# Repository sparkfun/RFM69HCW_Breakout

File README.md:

RFM69HCW Breakout Board
=================
The RFM69HCW is an inexpensive and versatile radio module that operates in the unlicensed ISM (Industry, Science, and Medicine) radio band. It's perfect for building inexpensive short-range wireless networks of sensors and actuators for home automation, citizen science, and more.

Specs
----------------

* Transmit power: -18dBm (0.016mW) to +20dBm (100mW) in 1dBm steps
* Receive sensitivity: down to -120dBm at 1.2kbps
* Modulation types: FSK GFSK MSK GMSK OOK
* Bit rates (FSK): 1.2kbps to 300kbps
* Voltage range: 1.8V to 3.6V
* Current consumption: 0.1uA sleep, 1.25mA standby, 16mA receive, 
* 130mA transmit (max)
* Encryption: AES 128-bit (optional)
* Packet buffer (FIFO): 66 bytes
* Dimensions: 0.8" x 1.1"

Product Versions
----------------

The RFM69HCW modules transmit in the [ISM band](http://en.wikipedia.org/wiki/ISM_band), which is reserved for short-range, low-power communications. SparkFun sells the RFM69HCW Breakout Board in two frequencies:

* [**RFM69HCW Breakout 915MHz (WRL-12775)**](https://www.sparkfun.com/products/12775)
* [**RFM69HCW Breakout 433MHz (WRL-12823)**](https://www.sparkfun.com/products/12823)

Broadly speaking, the 915MHz version is legal in [ITU region](http://en.wikipedia.org/wiki/ITU_region) 2 (North and South America, Australia, Greenland, Pacific Islands, Israel), and the 433MHz version is legal in [ITU region](http://en.wikipedia.org/wiki/ITU_region) 1 (Europe, Africa, Middle East, Russia). Other areas have mixed allocations; hobbyist use is not likely to be an issue, but if you're going to be deploying a lot of these or using them in a commercial product, check your local regulations.

Documentation
-------------------

* [**Hookup Guide**](https://learn.sparkfun.com/tutorials/rfm69hcw-hookup-guide)
* [**RFM69HCW Breakout Board Schematic**](https://github.com/sparkfun/RFM69HCW_Breakout/blob/master/documentation/RFM69HCW_BOB.pdf)
* [**RFM69HCW datasheet**](https://github.com/sparkfun/RFM69HCW_Breakout/blob/master/documentation/RFM69HCW-V1.1.pdf)
* [**HopeRF RFM69HCW product page (external link)**](http://www.hoperf.com/rf/fsk_module/RFM69HCW.htm)

Repository Contents
-------------------
* [**/Libraries/Arduino**](https://github.com/sparkfun/RFM69HCW_Breakout/tree/master/Libraries/Arduino) - Contains the [RFM69 library](https://github.com/LowPowerLab/RFM69) written by Felix Rusu of [LowPowerLab.com](lowpowerlab.com). See [https://github.com/LowPowerLab/RFM69](https://github.com/LowPowerLab/RFM69) for the most up-to-date version.

* [**/Libraries/Arduino/RFM69/examples**](https://github.com/sparkfun/RFM69HCW_Breakout/tree/master/Libraries/Arduino/RFM69/examples) - Example Arduino sketch showing how to use the SparkFun RFM69HCW breakout board. See the hook-up guide at [https://learn.sparkfun.com/tutorials/rfm69hcw-hookup-guide](https://learn.sparkfun.com/tutorials/rfm69hcw-hookup-guide) for wiring and usage details.

* [**/hardware**](https://github.com/sparkfun/RFM69HCW_Breakout/tree/master/hardware) - Eagle design files (.brd, .sch)

* [**/documentation**](https://github.com/sparkfun/RFM69HCW_Breakout/tree/master/documentation) - Datasheets, schematic, etc.

Attribution
-----------
We gratefully acknowledge Felix Rusu of [LowPowerLab.com](lowpowerlab.com) for his terrific [RFM69 library](https://github.com/LowPowerLab/RFM69), which runs on his very cool [Moteino](http://lowpowerlab.com/moteino/) hardware. A version of his library is included here for the convenience of SparkFun customers. Please see his [GitHub repository](https://github.com/LowPowerLab/RFM69) for the latest version.

License Information
-------------------
The hardware design is released under the [Creative Commons Attribution-ShareAlike 4.0 International](http://creativecommons.org/licenses/by-sa/4.0/) license.

Felix Rusu's RFM69 library is released under the [Creative Commons Attribution-ShareAlike 3.0](http://creativecommons.org/licenses/by-sa/3.0/) license. 

SparkFun's example code is based on Felix Rusu's work, and is thus released under the same [Creative Commons Attribution-ShareAlike 3.0](http://creativecommons.org/licenses/by-sa/3.0/) license.

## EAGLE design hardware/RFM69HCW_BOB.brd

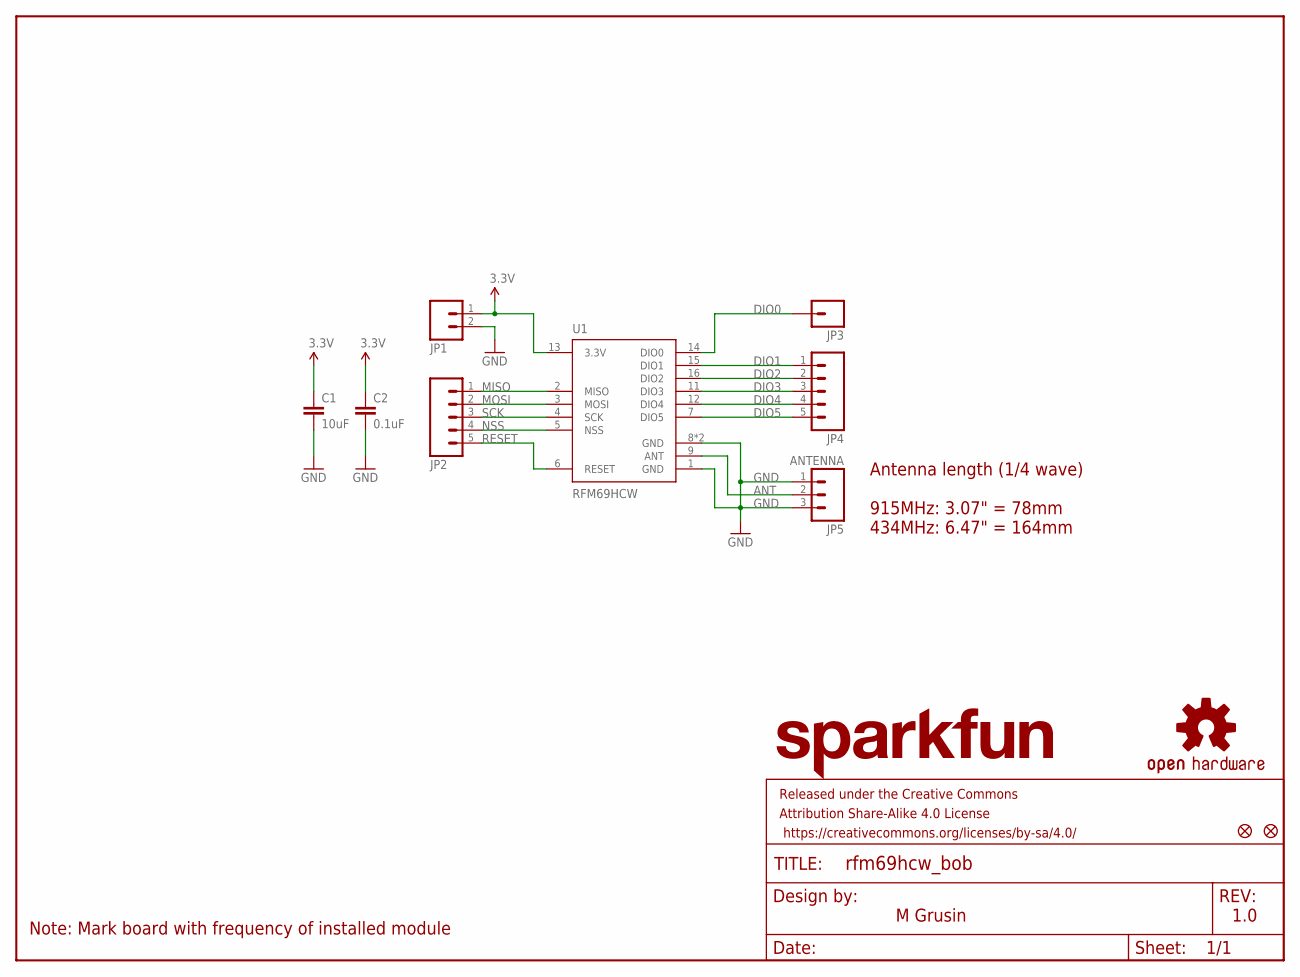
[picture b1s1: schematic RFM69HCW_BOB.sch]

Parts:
C1: 10uF; 1210
C2: 0.1uF; 0603-CAP
FID1, FID2: FIDUCIAL1X2; FIDUCIAL-1X2
FRAME1: FRAME-LETTER; CREATIVE_COMMONS
JP1: M021X02_NO_SILK; 1X02_NO_SILK
JP2, JP4: M05_ROUNDONLY_NOSILK; 1X05_ROUNDONLY_NOSILK
JP3: M01SMDNS; 1X01NS
JP5: ANTENNA; 1X03_ROUND_ONLY_NO_SILK
LOGO1: SFE_LOGO_NAME.1_INCH; SFE_LOGO_NAME_.1
LOGO2: OSHW-LOGOS; OSHW-LOGO-S
U1: RFM69HCW; RFM69HCW-XXXS2

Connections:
3.3V: C1.1, C2.1, JP1.1, U1.13 (3.3V)
ANT: JP5.2, U1.9 (ANT)
DIO0: JP3.1, U1.14 (DIO0)
DIO1: JP4.1, U1.15 (DIO1)
DIO2: JP4.2, U1.16 (DIO2)
DIO3: JP4.3, U1.11 (DIO3)
DIO4: JP4.4, U1.12 (DIO4)
DIO5: JP4.5, U1.7 (DIO5)
GND: C1.2, C2.2, JP1.2, JP5.1, JP5.3, U1.1 (GND), U1.8 (GND), U1.10 (GND)
MISO: JP2.1, U1.2 (MISO)
MOSI: JP2.2, U1.3 (MOSI)
NSS: JP2.4, U1.5 (NSS)
RESET: JP2.5, U1.6 (RESET)
SCK: JP2.3, U1.4 (SCK)

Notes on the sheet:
M Grusin
1.0
Note: Mark board with frequency of installed module
Antenna length (1/4 wave) 915MHz: 3.07" = 78mm 434MHz: 6.47" = 164mm

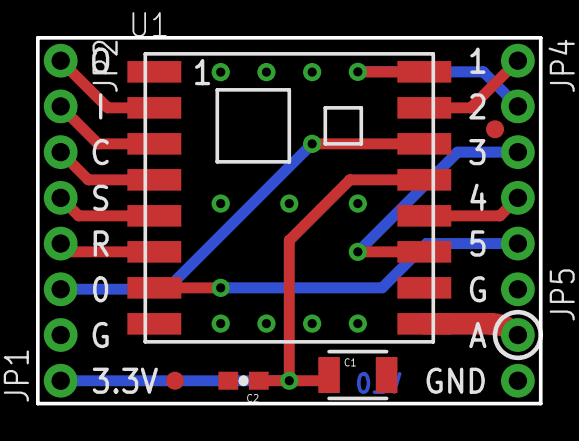
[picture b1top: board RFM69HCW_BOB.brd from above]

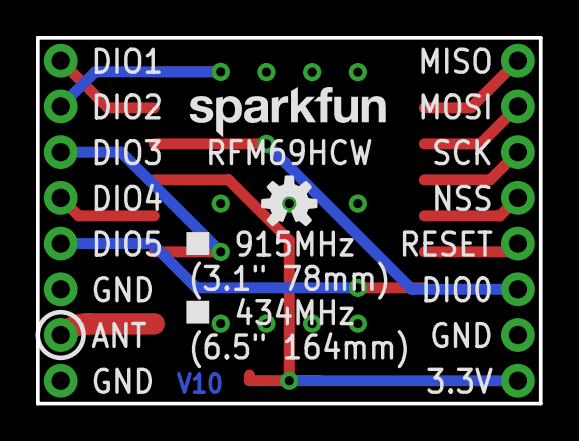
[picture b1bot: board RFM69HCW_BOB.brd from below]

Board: 2 copper layers, 27.9 x 20.3 mm, 13 parts (2 on the bottom side), 14 nets.

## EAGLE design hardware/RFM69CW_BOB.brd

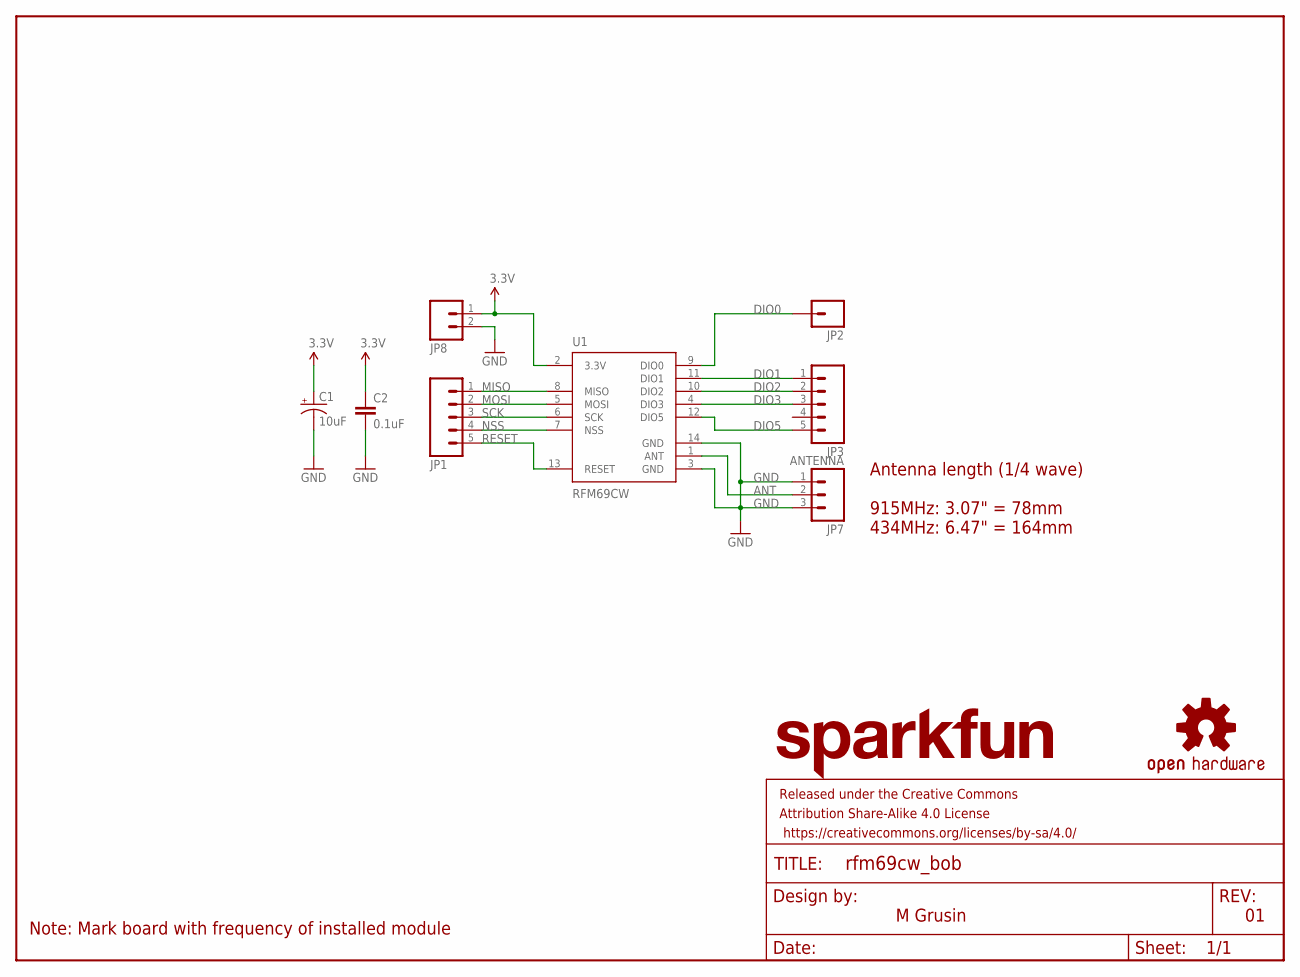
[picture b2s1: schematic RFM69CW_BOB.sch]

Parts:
C1: 10uF; EIA3216
C2: 0.1uF; 0603-CAP
FRAME1: FRAME-LETTER; CREATIVE_COMMONS
JP1, JP3: M05_ROUNDONLY_NOSILK; 1X05_ROUNDONLY_NOSILK
JP2: M01SMDNS; 1X01NS
JP7: ANTENNA; 1X03_ROUND_ONLY_NO_SILK
JP8: M021X02_NO_SILK; 1X02_NO_SILK
LOGO1: SFE_LOGO_NAME.1_INCH; SFE_LOGO_NAME_.1
LOGO2: OSHW-LOGOS; OSHW-LOGO-S
U1: RFM69CW; RFM69CW-XXXS2

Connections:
3.3V: C1.A (+), C2.1, JP8.1, U1.2 (3.3V)
ANT: JP7.2, U1.1 (ANT)
DIO0: JP2.1, U1.9 (DIO0)
DIO1: JP3.1, U1.11 (DIO1)
DIO2: JP3.2, U1.10 (DIO2)
DIO3: JP3.3, U1.4 (DIO3)
DIO5: JP3.5, U1.12 (DIO5)
GND: C1.C (-), C2.2, JP7.1, JP7.3, JP8.2, U1.3 (GND), U1.14 (GND)
MISO: JP1.1, U1.8 (MISO)
MOSI: JP1.2, U1.5 (MOSI)
NSS: JP1.4, U1.7 (NSS)
RESET: JP1.5, U1.13 (RESET)
SCK: JP1.3, U1.6 (SCK)

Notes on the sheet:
M Grusin
Note: Mark board with frequency of installed module
Antenna length (1/4 wave) 915MHz: 3.07" = 78mm 434MHz: 6.47" = 164mm

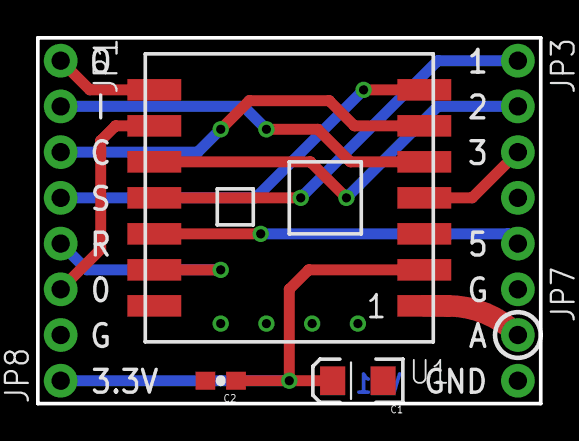
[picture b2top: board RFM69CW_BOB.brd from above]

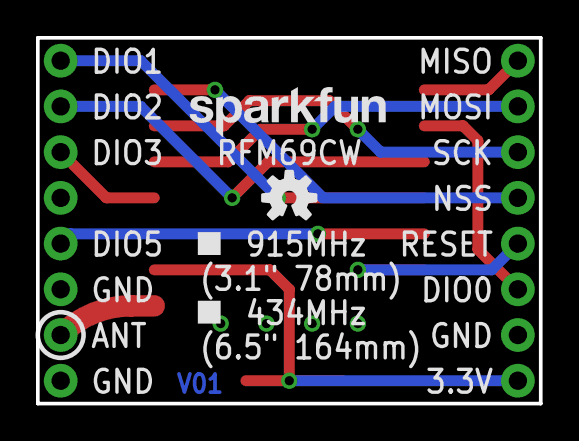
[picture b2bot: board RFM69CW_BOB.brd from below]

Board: 2 copper layers, 27.9 x 20.3 mm, 11 parts (2 on the bottom side), 13 nets.

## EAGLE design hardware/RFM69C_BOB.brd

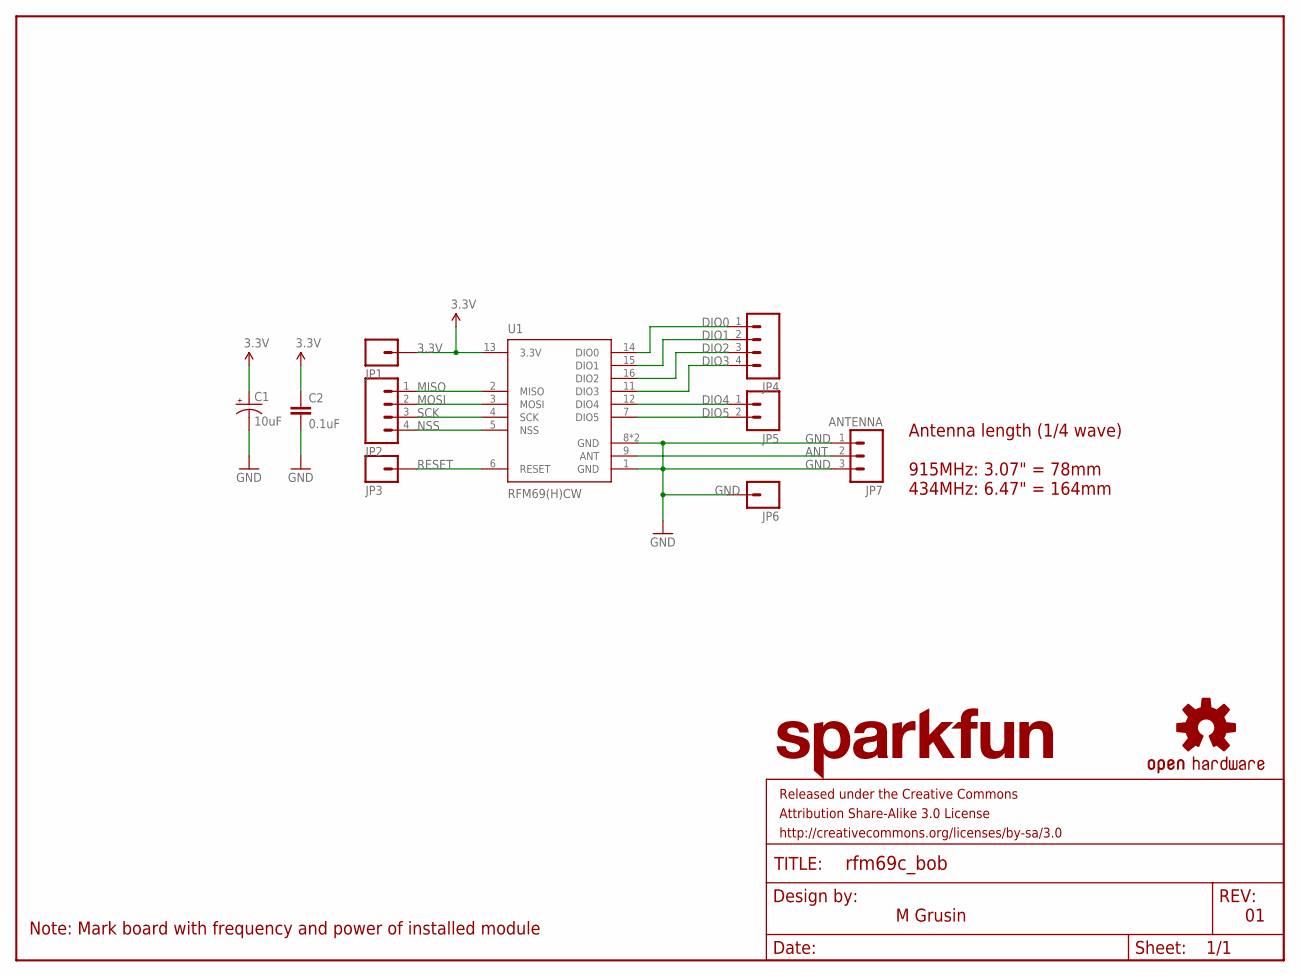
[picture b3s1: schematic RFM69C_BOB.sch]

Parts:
C1: 10uF; EIA3216
C2: 0.1uF; 0603-CAP
FRAME1: FRAME-LETTER; CREATIVE_COMMONS
JP1, JP3, JP6: M01SMDNS; 1X01NS
JP2, JP4: M041X04_NO_SILK_ROUND; 1X04_NO_SILK_ROUND
JP5: M021X02_NO_SILK; 1X02_NO_SILK
JP7: ANTENNA; 1X03_ROUND_ONLY_NO_SILK
LOGO1: SFE_LOGO_NAME.1_INCH; SFE_LOGO_NAME_.1
LOGO2: OSHW-LOGOS; OSHW-LOGO-S
U1: RFM69(H)CW; RFM69CS2

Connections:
3.3V: C1.A (+), C2.1, JP1.1, U1.13 (3.3V)
ANT: JP7.2, U1.9 (ANT)
DIO0: JP4.1, U1.14 (DIO0)
DIO1: JP4.2, U1.15 (DIO1)
DIO2: JP4.3, U1.16 (DIO2)
DIO3: JP4.4, U1.11 (DIO3)
DIO4: JP5.1, U1.12 (DIO4)
DIO5: JP5.2, U1.7 (DIO5)
GND: C1.C (-), C2.2, JP6.1, JP7.1, JP7.3, U1.1 (GND), U1.8 (GND), U1.10 (GND)
MISO: JP2.1, U1.2 (MISO)
MOSI: JP2.2, U1.3 (MOSI)
NSS: JP2.4, U1.5 (NSS)
RESET: JP3.1, U1.6 (RESET)
SCK: JP2.3, U1.4 (SCK)

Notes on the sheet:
M Grusin
Note: Mark board with frequency and power of installed module
Antenna length (1/4 wave) 915MHz: 3.07" = 78mm 434MHz: 6.47" = 164mm

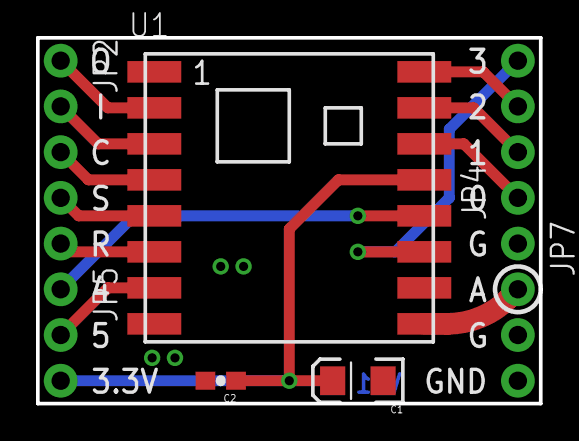
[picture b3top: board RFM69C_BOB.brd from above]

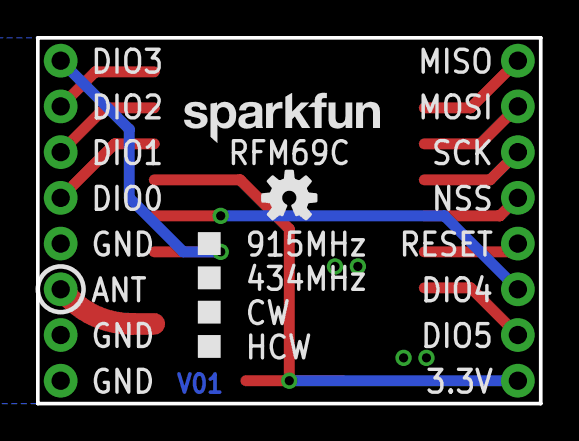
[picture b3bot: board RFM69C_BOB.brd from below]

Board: 2 copper layers, 27.9 x 20.3 mm, 13 parts (2 on the bottom side), 14 nets.

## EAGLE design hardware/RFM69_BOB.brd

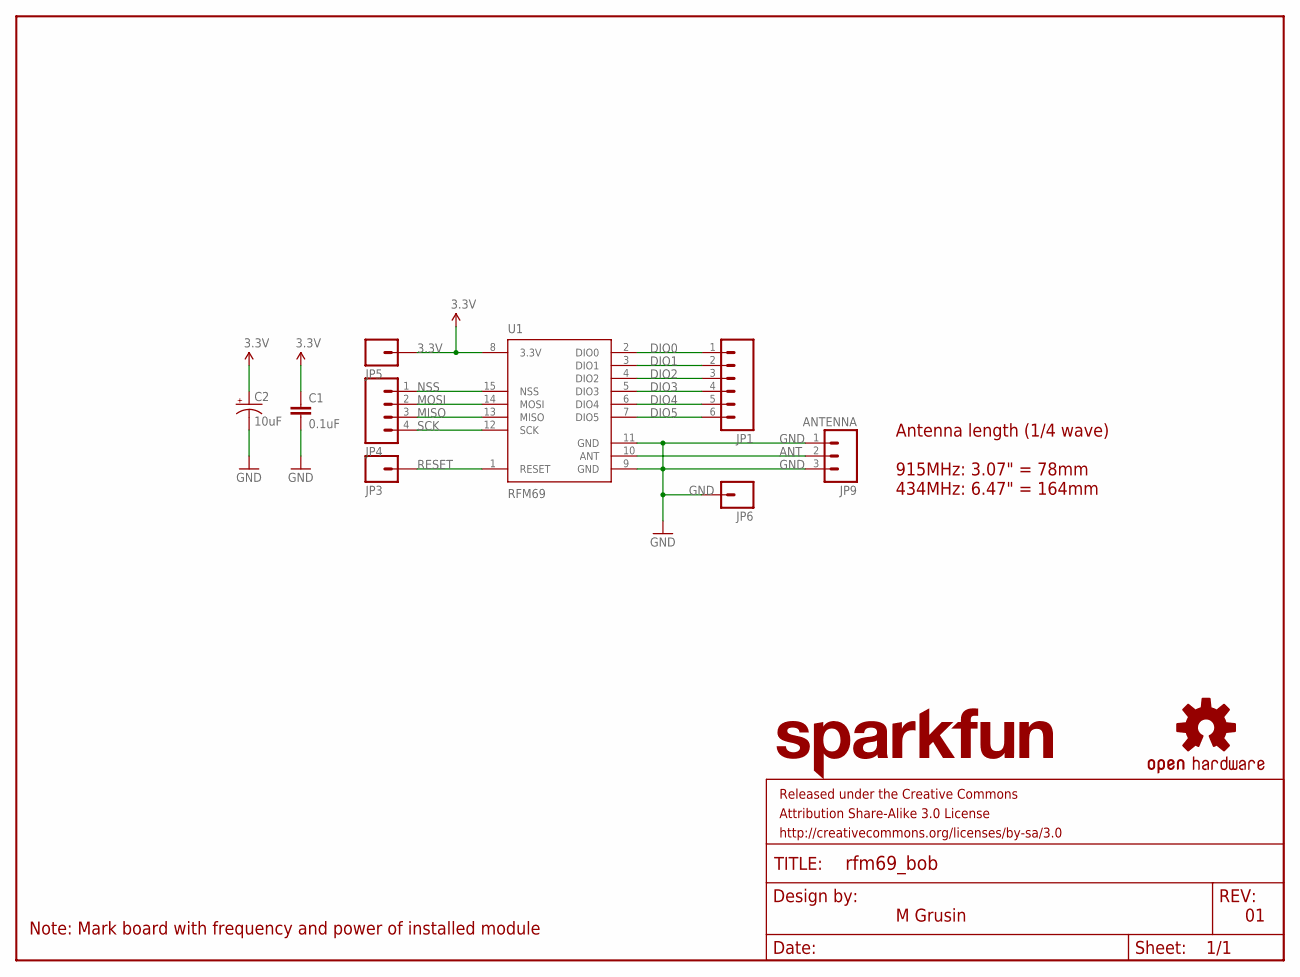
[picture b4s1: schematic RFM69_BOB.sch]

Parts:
C1: 0.1uF; 0603-CAP
C2: 10uF; EIA3216
FRAME1: FRAME-LETTER; CREATIVE_COMMONS
JP1: M06_NOSILK_ROUND; 1X06_NO_SILK_ROUND
JP3, JP5, JP6: M01SMDNS; 1X01NS
JP4: M041X04_NO_SILK_ROUND; 1X04_NO_SILK_ROUND
JP9: ANTENNA; 1X03_ROUND_ONLY_NO_SILK
LOGO1: SFE_LOGO_NAME.1_INCH; SFE_LOGO_NAME_.1
LOGO2: OSHW-LOGOS; OSHW-LOGO-S
U1: RFM69

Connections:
3.3V: C1.1, C2.A (+), JP5.1, U1.8 (3.3V)
ANT: JP9.2, U1.10 (ANT)
DIO0: JP1.1, U1.2 (DIO0)
DIO1: JP1.2, U1.3 (DIO1)
DIO2: JP1.3, U1.4 (DIO2)
DIO3: JP1.4, U1.5 (DIO3)
DIO4: JP1.5, U1.6 (DIO4)
DIO5: JP1.6, U1.7 (DIO5)
GND: C1.2, C2.C (-), JP6.1, JP9.1, JP9.3, U1.9 (GND), U1.11 (GND)
MISO: JP4.3, U1.13 (MISO)
MOSI: JP4.2, U1.14 (MOSI)
NSS: JP4.1, U1.15 (NSS)
RESET: JP3.1, U1.1 (RESET)
SCK: JP4.4, U1.12 (SCK)

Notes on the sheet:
M Grusin
Note: Mark board with frequency and power of installed module
Antenna length (1/4 wave) 915MHz: 3.07" = 78mm 434MHz: 6.47" = 164mm

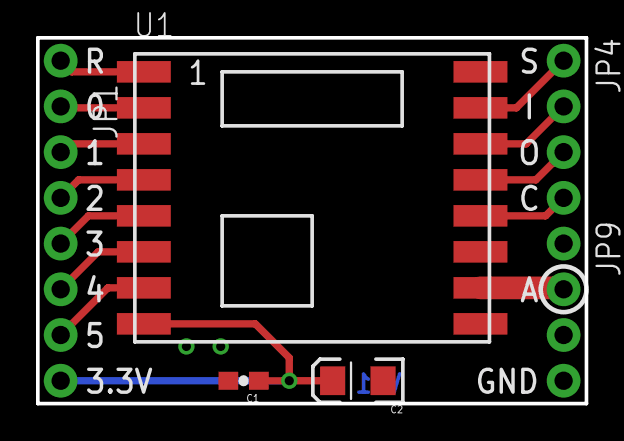
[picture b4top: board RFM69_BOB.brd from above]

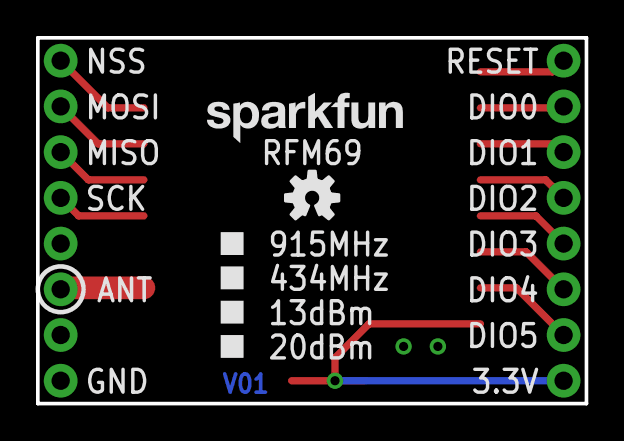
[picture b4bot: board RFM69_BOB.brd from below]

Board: 2 copper layers, 30.5 x 20.3 mm, 12 parts (2 on the bottom side), 14 nets.

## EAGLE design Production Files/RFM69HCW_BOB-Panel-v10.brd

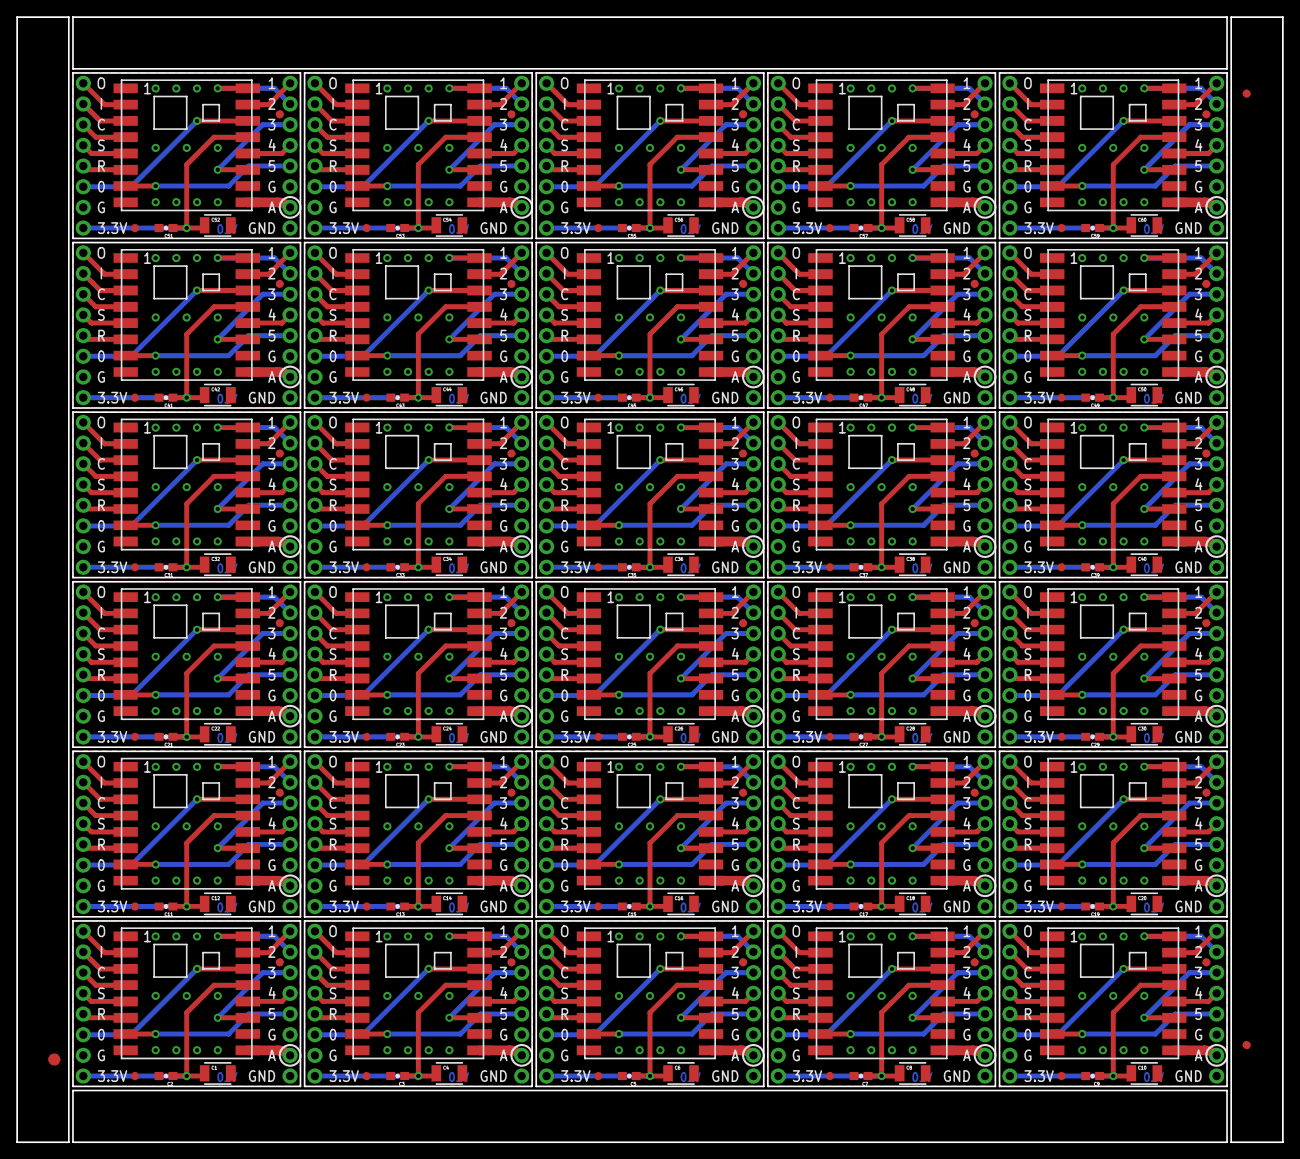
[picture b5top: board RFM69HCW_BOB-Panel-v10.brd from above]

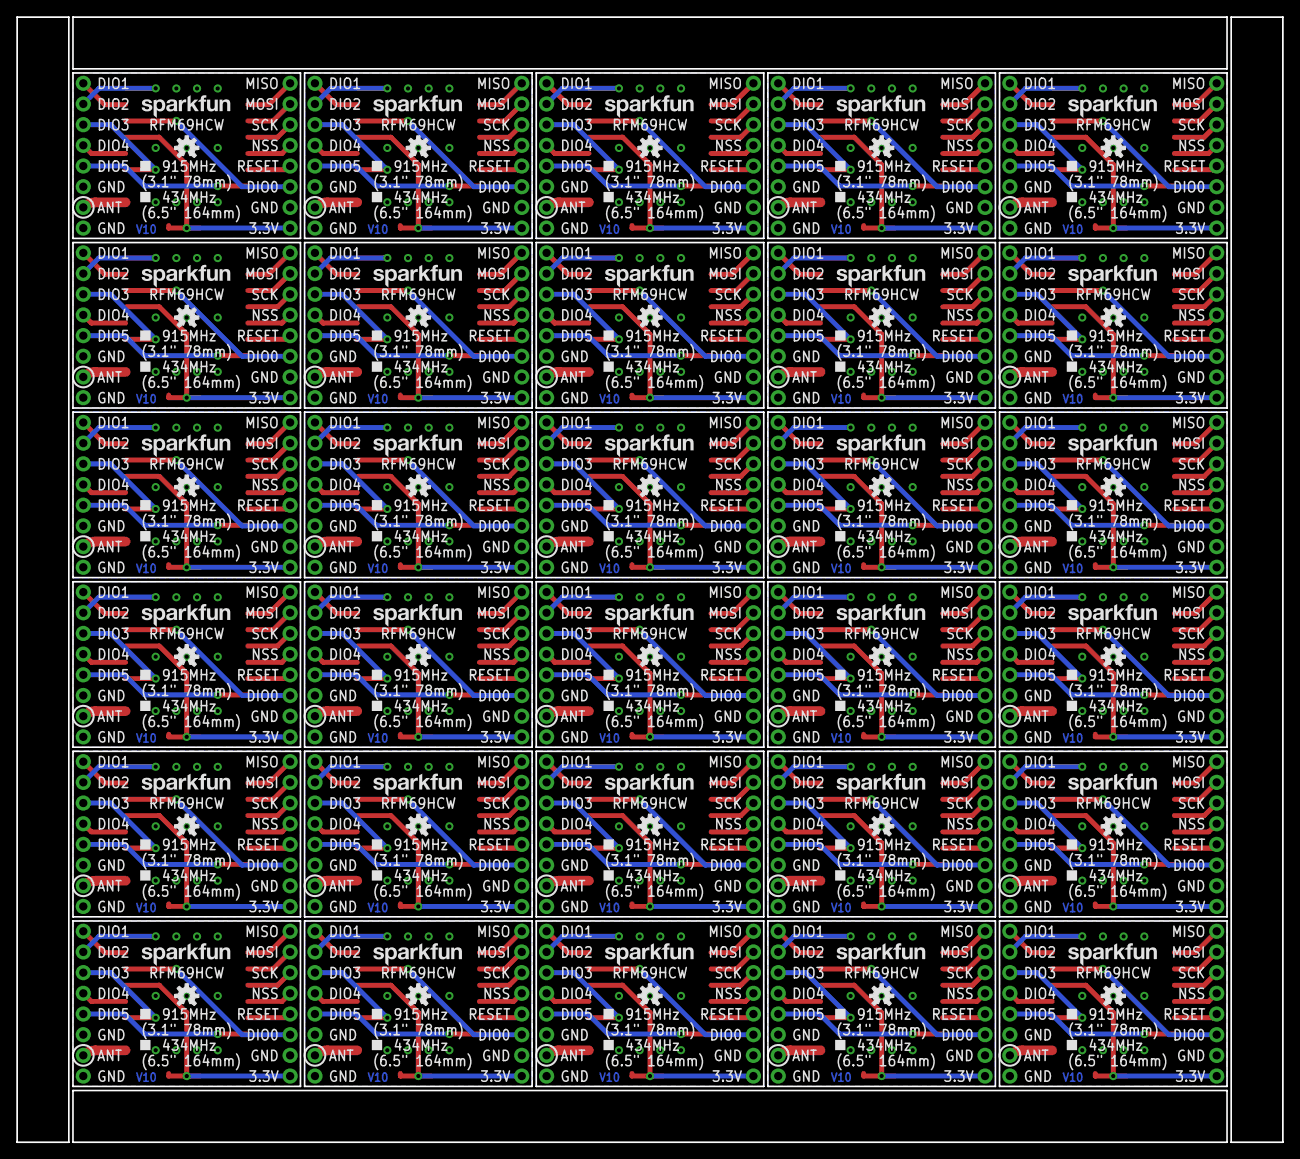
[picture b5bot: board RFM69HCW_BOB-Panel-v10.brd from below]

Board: 2 copper layers, 155.4 x 138.2 mm, 363 parts (60 on the bottom side), 420 nets.

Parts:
C1, C4, C6, C8, C10, C12, C14, C16, C18, C20, C22, C24, C26, C28, C30, C32, C34, C36, C38, C40, C42, C44, C46, C48, C50, C52, C54, C56, C58, C60: 10uF; 1210
C2, C3, C5, C7, C9, C11, C13, C15, C17, C19, C21, C23, C25, C27, C29, C31, C33, C35, C37, C39, C41, C43, C45, C47, C49, C51, C53, C55, C57, C59: 0.1uF; 0603-CAP
E$1: FIDUCIAL-1.5X3
E$4, E$6: FIDUCIAL-1X2
FID1, FID2, FID3, FID4, FID5, FID6, FID7, FID8, FID9, FID10, FID11, FID12, FID13, FID14, FID15, FID16, FID17, FID18, FID19, FID20, FID21, FID22, FID23, FID24, FID25, FID26, FID27, FID28, FID29, FID30, FID31, FID32, FID33, FID34, FID35, FID36, FID37, FID38, FID39, FID40, FID41, FID42, FID43, FID44, FID45, FID46, FID47, FID48, FID49, FID50, FID51, FID52, FID53, FID54, FID55, FID56, FID57, FID58, FID59, FID60: FIDUCIAL1X2; FIDUCIAL-1X2
JP1, JP7, JP12, JP17, JP22, JP27, JP32, JP37, JP42, JP47, JP52, JP57, JP62, JP67, JP72, JP77, JP82, JP87, JP92, JP97, JP102, JP107, JP112, JP117, JP122, JP127, JP132, JP137, JP142, JP147: 1X02_NO_SILK
JP2, JP4, JP8, JP10, JP13, JP15, JP18, JP20, JP23, JP25, JP28, JP30, JP33, JP35, JP38, JP40, JP43, JP45, JP48, JP50, JP53, JP55, JP58, JP60, JP63, JP65, JP68, JP70, JP73, JP75, JP78, JP80, JP83, JP85, JP88, JP90, JP93, JP95, JP98, JP100, JP103, JP105, JP108, JP110, JP113, JP115, JP118, JP120, JP123, JP125, JP128, JP130, JP133, JP135, JP138, JP140, JP143, JP145, JP148, JP150: 1X05_ROUNDONLY_NOSILK
JP3, JP9, JP14, JP19, JP24, JP29, JP34, JP39, JP44, JP49, JP54, JP59, JP64, JP69, JP74, JP79, JP84, JP89, JP94, JP99, JP104, JP109, JP114, JP119, JP124, JP129, JP134, JP139, JP144, JP149: 1X01NS
JP5, JP6, JP11, JP16, JP21, JP26, JP31, JP36, JP41, JP46, JP51, JP56, JP61, JP66, JP71, JP76, JP81, JP86, JP91, JP96, JP101, JP106, JP111, JP116, JP121, JP126, JP131, JP136, JP141, JP146: ANTENNA; 1X03_ROUND_ONLY_NO_SILK
LOGO1, LOGO3, LOGO5, LOGO7, LOGO9, LOGO11, LOGO13, LOGO15, LOGO17, LOGO19, LOGO21, LOGO23, LOGO25, LOGO27, LOGO29, LOGO31, LOGO33, LOGO35, LOGO37, LOGO39, LOGO41, LOGO43, LOGO45, LOGO47, LOGO49, LOGO51, LOGO53, LOGO55, LOGO57, LOGO59: SFE_LOGO_NAME.1_INCH; SFE_LOGO_NAME_.1
LOGO2, LOGO4, LOGO6, LOGO8, LOGO10, LOGO12, LOGO14, LOGO16, LOGO18, LOGO20, LOGO22, LOGO24, LOGO26, LOGO28, LOGO30, LOGO32, LOGO34, LOGO36, LOGO38, LOGO40, LOGO42, LOGO44, LOGO46, LOGO48, LOGO50, LOGO52, LOGO54, LOGO56, LOGO58, LOGO60: OSHW-LOGOS; OSHW-LOGO-S
U1, U2, U3, U4, U5, U6, U7, U8, U9, U10, U11, U12, U13, U14, U15, U16, U17, U18, U19, U20, U21, U22, U23, U24, U25, U26, U27, U28, U29, U30: RFM69HCW; RFM69HCW-XXXS2

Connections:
3.3V: C1.1, C2.1, JP1.1, U1.13
3.3V1: C3.1, C4.1, JP7.1, U2.13
3.3V2: C5.1, C6.1, JP12.1, U3.13
3.3V3: C7.1, C8.1, JP17.1, U4.13
3.3V4: C9.1, C10.1, JP22.1, U5.13
3.3V5: C11.1, C12.1, JP27.1, U6.13
3.3V6: C13.1, C14.1, JP32.1, U7.13
3.3V7: C15.1, C16.1, JP37.1, U8.13
3.3V8: C17.1, C18.1, JP42.1, U9.13
3.3V9: C19.1, C20.1, JP47.1, U10.13
3.3V10: C21.1, C22.1, JP52.1, U11.13
3.3V11: C23.1, C24.1, JP57.1, U12.13
3.3V12: C25.1, C26.1, JP62.1, U13.13
3.3V13: C27.1, C28.1, JP67.1, U14.13
3.3V14: C29.1, C30.1, JP72.1, U15.13
3.3V15: C31.1, C32.1, JP77.1, U16.13
3.3V16: C33.1, C34.1, JP82.1, U17.13
3.3V17: C35.1, C36.1, JP87.1, U18.13
3.3V18: C37.1, C38.1, JP92.1, U19.13
3.3V19: C39.1, C40.1, JP97.1, U20.13
3.3V20: C41.1, C42.1, JP102.1, U21.13
3.3V21: C43.1, C44.1, JP107.1, U22.13
3.3V22: C45.1, C46.1, JP112.1, U23.13
3.3V23: C47.1, C48.1, JP117.1, U24.13
3.3V24: C49.1, C50.1, JP122.1, U25.13
3.3V25: C51.1, C52.1, JP127.1, U26.13
3.3V26: C53.1, C54.1, JP132.1, U27.13
3.3V27: C55.1, C56.1, JP137.1, U28.13
3.3V28: C57.1, C58.1, JP142.1, U29.13
3.3V29: C59.1, C60.1, JP147.1, U30.13
ANT: JP5.2, U1.9
ANT1: JP6.2, U2.9
ANT2: JP11.2, U3.9
ANT3: JP16.2, U4.9
ANT4: JP21.2, U5.9
ANT5: JP26.2, U6.9
ANT6: JP31.2, U7.9
ANT7: JP36.2, U8.9
ANT8: JP41.2, U9.9
ANT9: JP46.2, U10.9
ANT10: JP51.2, U11.9
ANT11: JP56.2, U12.9
ANT12: JP61.2, U13.9
ANT13: JP66.2, U14.9
ANT14: JP71.2, U15.9
ANT15: JP76.2, U16.9
ANT16: JP81.2, U17.9
ANT17: JP86.2, U18.9
ANT18: JP91.2, U19.9
ANT19: JP96.2, U20.9
ANT20: JP101.2, U21.9
ANT21: JP106.2, U22.9
ANT22: JP111.2, U23.9
ANT23: JP116.2, U24.9
ANT24: JP121.2, U25.9
ANT25: JP126.2, U26.9
ANT26: JP131.2, U27.9
ANT27: JP136.2, U28.9
ANT28: JP141.2, U29.9
ANT29: JP146.2, U30.9
DIO0: JP3.1, U1.14
DIO1: JP4.1, U1.15
DIO2: JP4.2, U1.16
DIO3: JP4.3, U1.11
DIO4: JP4.4, U1.12
DIO5: JP4.5, U1.7
DIO6: JP9.1, U2.14
DIO7: JP10.1, U2.15
DIO8: JP10.2, U2.16
DIO9: JP10.3, U2.11
DIO10: JP10.5, U2.7
DIO11: JP10.4, U2.12
DIO12: JP14.1, U3.14
DIO13: JP15.1, U3.15
DIO14: JP15.2, U3.16
DIO15: JP15.3, U3.11
DIO16: JP15.5, U3.7
DIO17: JP15.4, U3.12
DIO18: JP19.1, U4.14
DIO19: JP20.1, U4.15
DIO20: JP20.2, U4.16
DIO21: JP20.3, U4.11
DIO22: JP20.5, U4.7
DIO23: JP20.4, U4.12
DIO24: JP24.1, U5.14
DIO25: JP25.1, U5.15
DIO26: JP25.2, U5.16
DIO27: JP25.3, U5.11
DIO28: JP25.5, U5.7
DIO29: JP25.4, U5.12
DIO30: JP29.1, U6.14
DIO31: JP30.1, U6.15
DIO32: JP30.2, U6.16
DIO33: JP30.3, U6.11
DIO34: JP30.5, U6.7
DIO35: JP30.4, U6.12
DIO36: JP34.1, U7.14
DIO37: JP35.1, U7.15
DIO38: JP35.2, U7.16
DIO39: JP35.3, U7.11
DIO40: JP35.5, U7.7
DIO41: JP35.4, U7.12
DIO42: JP39.1, U8.14
DIO43: JP40.1, U8.15
DIO44: JP40.2, U8.16
DIO45: JP40.3, U8.11
DIO46: JP40.5, U8.7
DIO47: JP40.4, U8.12
DIO48: JP44.1, U9.14
DIO49: JP45.1, U9.15
DIO50: JP45.2, U9.16
DIO51: JP45.3, U9.11
DIO52: JP45.5, U9.7
DIO53: JP45.4, U9.12
DIO54: JP49.1, U10.14
DIO55: JP50.1, U10.15
DIO56: JP50.2, U10.16
DIO57: JP50.3, U10.11
DIO58: JP50.5, U10.7
DIO59: JP50.4, U10.12
DIO60: JP54.1, U11.14
DIO61: JP55.1, U11.15
DIO62: JP55.2, U11.16
DIO63: JP55.3, U11.11
DIO64: JP55.5, U11.7
DIO65: JP55.4, U11.12
DIO66: JP59.1, U12.14
DIO67: JP60.1, U12.15
DIO68: JP60.2, U12.16
DIO69: JP60.3, U12.11
DIO70: JP60.5, U12.7
DIO71: JP60.4, U12.12
DIO72: JP64.1, U13.14
DIO73: JP65.1, U13.15
DIO74: JP65.2, U13.16
DIO75: JP65.3, U13.11
DIO76: JP65.5, U13.7
DIO77: JP65.4, U13.12
DIO78: JP69.1, U14.14
DIO79: JP70.1, U14.15
DIO80: JP70.2, U14.16
DIO81: JP70.3, U14.11
DIO82: JP70.5, U14.7
DIO83: JP70.4, U14.12
DIO84: JP74.1, U15.14
DIO85: JP75.1, U15.15
DIO86: JP75.2, U15.16
DIO87: JP75.3, U15.11
DIO88: JP75.5, U15.7
DIO89: JP75.4, U15.12
DIO90: JP79.1, U16.14
DIO91: JP80.1, U16.15
DIO92: JP80.2, U16.16
DIO93: JP80.3, U16.11
DIO94: JP80.5, U16.7
DIO95: JP80.4, U16.12
DIO96: JP84.1, U17.14
DIO97: JP85.1, U17.15
DIO98: JP85.2, U17.16
DIO99: JP85.3, U17.11
DIO100: JP85.5, U17.7
DIO101: JP85.4, U17.12
DIO102: JP89.1, U18.14
DIO103: JP90.1, U18.15
DIO104: JP90.2, U18.16
DIO105: JP90.3, U18.11
DIO106: JP90.5, U18.7
DIO107: JP90.4, U18.12
DIO108: JP94.1, U19.14
DIO109: JP95.1, U19.15
DIO110: JP95.2, U19.16
DIO111: JP95.3, U19.11
DIO112: JP95.5, U19.7
DIO113: JP95.4, U19.12
DIO114: JP99.1, U20.14
DIO115: JP100.1, U20.15
DIO116: JP100.2, U20.16
DIO117: JP100.3, U20.11
DIO118: JP100.5, U20.7
DIO119: JP100.4, U20.12
DIO120: JP104.1, U21.14
DIO121: JP105.1, U21.15
DIO122: JP105.2, U21.16
DIO123: JP105.3, U21.11
DIO124: JP105.5, U21.7
DIO125: JP105.4, U21.12
DIO126: JP109.1, U22.14
DIO127: JP110.1, U22.15
DIO128: JP110.2, U22.16
DIO129: JP110.3, U22.11
DIO130: JP110.5, U22.7
DIO131: JP110.4, U22.12
DIO132: JP114.1, U23.14
DIO133: JP115.1, U23.15
DIO134: JP115.2, U23.16
DIO135: JP115.3, U23.11
DIO136: JP115.5, U23.7
DIO137: JP115.4, U23.12
DIO138: JP119.1, U24.14
DIO139: JP120.1, U24.15
DIO140: JP120.2, U24.16
DIO141: JP120.3, U24.11
DIO142: JP120.5, U24.7
DIO143: JP120.4, U24.12
DIO144: JP124.1, U25.14
DIO145: JP125.1, U25.15
DIO146: JP125.2, U25.16
DIO147: JP125.3, U25.11
DIO148: JP125.5, U25.7
DIO149: JP125.4, U25.12
DIO150: JP129.1, U26.14
DIO151: JP130.1, U26.15
DIO152: JP130.2, U26.16
DIO153: JP130.3, U26.11
DIO154: JP130.5, U26.7
DIO155: JP130.4, U26.12
DIO156: JP134.1, U27.14
DIO157: JP135.1, U27.15
DIO158: JP135.2, U27.16
DIO159: JP135.3, U27.11
DIO160: JP135.5, U27.7
DIO161: JP135.4, U27.12
DIO162: JP139.1, U28.14
DIO163: JP140.1, U28.15
DIO164: JP140.2, U28.16
DIO165: JP140.3, U28.11
DIO166: JP140.5, U28.7
DIO167: JP140.4, U28.12
DIO168: JP144.1, U29.14
DIO169: JP145.1, U29.15
DIO170: JP145.2, U29.16
DIO171: JP145.3, U29.11
DIO172: JP145.5, U29.7
DIO173: JP145.4, U29.12
DIO174: JP149.1, U30.14
DIO175: JP150.1, U30.15
DIO176: JP150.2, U30.16
DIO177: JP150.3, U30.11
DIO178: JP150.5, U30.7
DIO179: JP150.4, U30.12
GND: C1.2, C2.2, JP1.2, JP5.1, JP5.3, U1.1, U1.8, U1.10
GND1: C3.2, C4.2, JP6.1, JP6.3, JP7.2, U2.1, U2.8, U2.10
GND2: C5.2, C6.2, JP11.1, JP11.3, JP12.2, U3.1, U3.8, U3.10
GND3: C7.2, C8.2, JP16.1, JP16.3, JP17.2, U4.1, U4.8, U4.10
GND4: C9.2, C10.2, JP21.1, JP21.3, JP22.2, U5.1, U5.8, U5.10
GND5: C11.2, C12.2, JP26.1, JP26.3, JP27.2, U6.1, U6.8, U6.10
GND6: C13.2, C14.2, JP31.1, JP31.3, JP32.2, U7.1, U7.8, U7.10
GND7: C15.2, C16.2, JP36.1, JP36.3, JP37.2, U8.1, U8.8, U8.10
GND8: C17.2, C18.2, JP41.1, JP41.3, JP42.2, U9.1, U9.8, U9.10
GND9: C19.2, C20.2, JP46.1, JP46.3, JP47.2, U10.1, U10.8, U10.10
GND10: C21.2, C22.2, JP51.1, JP51.3, JP52.2, U11.1, U11.8, U11.10
GND11: C23.2, C24.2, JP56.1, JP56.3, JP57.2, U12.1, U12.8, U12.10
GND12: C25.2, C26.2, JP61.1, JP61.3, JP62.2, U13.1, U13.8, U13.10
GND13: C27.2, C28.2, JP66.1, JP66.3, JP67.2, U14.1, U14.8, U14.10
GND14: C29.2, C30.2, JP71.1, JP71.3, JP72.2, U15.1, U15.8, U15.10
GND15: C31.2, C32.2, JP76.1, JP76.3, JP77.2, U16.1, U16.8, U16.10
GND16: C33.2, C34.2, JP81.1, JP81.3, JP82.2, U17.1, U17.8, U17.10
GND17: C35.2, C36.2, JP86.1, JP86.3, JP87.2, U18.1, U18.8, U18.10
GND18: C37.2, C38.2, JP91.1, JP91.3, JP92.2, U19.1, U19.8, U19.10
GND19: C39.2, C40.2, JP96.1, JP96.3, JP97.2, U20.1, U20.8, U20.10
GND20: C41.2, C42.2, JP101.1, JP101.3, JP102.2, U21.1, U21.8, U21.10
GND21: C43.2, C44.2, JP106.1, JP106.3, JP107.2, U22.1, U22.8, U22.10
GND22: C45.2, C46.2, JP111.1, JP111.3, JP112.2, U23.1, U23.8, U23.10
GND23: C47.2, C48.2, JP116.1, JP116.3, JP117.2, U24.1, U24.8, U24.10
GND24: C49.2, C50.2, JP121.1, JP121.3, JP122.2, U25.1, U25.8, U25.10
GND25: C51.2, C52.2, JP126.1, JP126.3, JP127.2, U26.1, U26.8, U26.10
GND26: C53.2, C54.2, JP131.1, JP131.3, JP132.2, U27.1, U27.8, U27.10
GND27: C55.2, C56.2, JP136.1, JP136.3, JP137.2, U28.1, U28.8, U28.10
GND28: C57.2, C58.2, JP141.1, JP141.3, JP142.2, U29.1, U29.8, U29.10
GND29: C59.2, C60.2, JP146.1, JP146.3, JP147.2, U30.1, U30.8, U30.10
MISO: JP2.1, U1.2
MISO1: JP8.1, U2.2
MISO2: JP13.1, U3.2
MISO3: JP18.1, U4.2
MISO4: JP23.1, U5.2
MISO5: JP28.1, U6.2
MISO6: JP33.1, U7.2
MISO7: JP38.1, U8.2
MISO8: JP43.1, U9.2
MISO9: JP48.1, U10.2
MISO10: JP53.1, U11.2
MISO11: JP58.1, U12.2
MISO12: JP63.1, U13.2
MISO13: JP68.1, U14.2
MISO14: JP73.1, U15.2
MISO15: JP78.1, U16.2
MISO16: JP83.1, U17.2
MISO17: JP88.1, U18.2
MISO18: JP93.1, U19.2
MISO19: JP98.1, U20.2
MISO20: JP103.1, U21.2
MISO21: JP108.1, U22.2
MISO22: JP113.1, U23.2
MISO23: JP118.1, U24.2
MISO24: JP123.1, U25.2
MISO25: JP128.1, U26.2
MISO26: JP133.1, U27.2
MISO27: JP138.1, U28.2
MISO28: JP143.1, U29.2
MISO29: JP148.1, U30.2
MOSI: JP2.2, U1.3
MOSI1: JP8.2, U2.3
MOSI2: JP13.2, U3.3
MOSI3: JP18.2, U4.3
MOSI4: JP23.2, U5.3
MOSI5: JP28.2, U6.3
MOSI6: JP33.2, U7.3
MOSI7: JP38.2, U8.3
MOSI8: JP43.2, U9.3
MOSI9: JP48.2, U10.3
MOSI10: JP53.2, U11.3
MOSI11: JP58.2, U12.3
MOSI12: JP63.2, U13.3
MOSI13: JP68.2, U14.3
MOSI14: JP73.2, U15.3
MOSI15: JP78.2, U16.3
MOSI16: JP83.2, U17.3
MOSI17: JP88.2, U18.3
MOSI18: JP93.2, U19.3
MOSI19: JP98.2, U20.3
MOSI20: JP103.2, U21.3
MOSI21: JP108.2, U22.3
MOSI22: JP113.2, U23.3
MOSI23: JP118.2, U24.3
MOSI24: JP123.2, U25.3
MOSI25: JP128.2, U26.3
MOSI26: JP133.2, U27.3
MOSI27: JP138.2, U28.3
MOSI28: JP143.2, U29.3
MOSI29: JP148.2, U30.3
NSS: JP2.4, U1.5
NSS1: JP8.4, U2.5
NSS2: JP13.4, U3.5
NSS3: JP18.4, U4.5
NSS4: JP23.4, U5.5
NSS5: JP28.4, U6.5
NSS6: JP33.4, U7.5
NSS7: JP38.4, U8.5
NSS8: JP43.4, U9.5
NSS9: JP48.4, U10.5
NSS10: JP53.4, U11.5
NSS11: JP58.4, U12.5
NSS12: JP63.4, U13.5
NSS13: JP68.4, U14.5
NSS14: JP73.4, U15.5
NSS15: JP78.4, U16.5
NSS16: JP83.4, U17.5
NSS17: JP88.4, U18.5
NSS18: JP93.4, U19.5
NSS19: JP98.4, U20.5
NSS20: JP103.4, U21.5
NSS21: JP108.4, U22.5
NSS22: JP113.4, U23.5
NSS23: JP118.4, U24.5
NSS24: JP123.4, U25.5
NSS25: JP128.4, U26.5
NSS26: JP133.4, U27.5
NSS27: JP138.4, U28.5
NSS28: JP143.4, U29.5
NSS29: JP148.4, U30.5
RESET: JP2.5, U1.6
RESET1: JP8.5, U2.6
RESET2: JP13.5, U3.6
RESET3: JP18.5, U4.6
RESET4: JP23.5, U5.6
RESET5: JP28.5, U6.6
RESET6: JP33.5, U7.6
RESET7: JP38.5, U8.6
RESET8: JP43.5, U9.6
RESET9: JP48.5, U10.6
RESET10: JP53.5, U11.6
RESET11: JP58.5, U12.6
RESET12: JP63.5, U13.6
RESET13: JP68.5, U14.6
RESET14: JP73.5, U15.6
RESET15: JP78.5, U16.6
RESET16: JP83.5, U17.6
RESET17: JP88.5, U18.6
RESET18: JP93.5, U19.6
RESET19: JP98.5, U20.6
RESET20: JP103.5, U21.6
RESET21: JP108.5, U22.6
RESET22: JP113.5, U23.6
RESET23: JP118.5, U24.6
RESET24: JP123.5, U25.6
RESET25: JP128.5, U26.6
RESET26: JP133.5, U27.6
RESET27: JP138.5, U28.6
RESET28: JP143.5, U29.6
RESET29: JP148.5, U30.6
SCK: JP2.3, U1.4
SCK1: JP8.3, U2.4
SCK2: JP13.3, U3.4
SCK3: JP18.3, U4.4
SCK4: JP23.3, U5.4
SCK5: JP28.3, U6.4
SCK6: JP33.3, U7.4
SCK7: JP38.3, U8.4
SCK8: JP43.3, U9.4
SCK9: JP48.3, U10.4
SCK10: JP53.3, U11.4
SCK11: JP58.3, U12.4
SCK12: JP63.3, U13.4
SCK13: JP68.3, U14.4
SCK14: JP73.3, U15.4
SCK15: JP78.3, U16.4
SCK16: JP83.3, U17.4
SCK17: JP88.3, U18.4
SCK18: JP93.3, U19.4
SCK19: JP98.3, U20.4
SCK20: JP103.3, U21.4
SCK21: JP108.3, U22.4
SCK22: JP113.3, U23.4
SCK23: JP118.3, U24.4
SCK24: JP123.3, U25.4
SCK25: JP128.3, U26.4
SCK26: JP133.3, U27.4
SCK27: JP138.3, U28.4
SCK28: JP143.3, U29.4
SCK29: JP148.3, U30.4

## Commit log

2014-02-20 Changed part to 'C' (compact) variant
    New footprint, changed name to ensure proper variant is used (RFM69CW or
    RFM69HCW)
2014-02-21 Added datasheets
2014-02-21 Renamed board to HCW
    C (low power) and HC (high power) parts have different footprints;
    renamed board and part for HC footprint.
2014-02-21 Minor silk updates
2014-02-21 Deleted incorrect "C" variant
2014-03-17 HCW BOB to 1.0, CW BOB to 0.1
2014-03-18 Added fiducials to HCW BOB, initial example code
2014-03-18 initial example code
2014-03-18 Changed capacitor, removed C variant
    Changed C1 to CAP-9824 (10uF ceramic for better transient response)
    Removed RFM69C (low power) for future BOB
2014-03-18 Changed version to 1.0 for reds
2014-03-21 Minor silk and routing tweaks for reds
2014-03-21 Renamed repo, deleted unused CW datasheet
2014-03-21 cleanup: doc folder
2014-03-21 Added RFM69 library, readme
2014-03-21 cleanup for reds
2014-03-25 created panel v10
2014-04-03 More example code: simple_chat_with_ACK
    Simple_chat_with_ACK: set up #defines with node numbers, upload, send
    text to board, CR sends message. Turn on "promiscuous mode" to see all
    messages. Uses ACK to verify reception (or not).
2014-04-19 eagleup
2014-05-28 File cleanup
2014-05-31 New test code versions
2016-03-22 Added schematic PDF, code update
2016-03-22 Moved schematic PDF to docs
2016-04-28 broad changes for product release
2016-04-28 Added picture to description
2016-04-28 minor description edits
2016-04-28 minor edits
2016-04-28 minor edit
2019-11-04 Bug fix for use with Pro Micro
    Bug fix for use with Pro Micro

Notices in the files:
parts and their libraries:
SparkFun-Aesthetics: Licensing: CC v3.0 Share-Alike You are welcome to use this library for commercial purposes.
SparkFun-Retired: Licensing:Creative Commons ShareAlike 4.0 International - https://creativecommons.org/licenses/by-sa/4.0
